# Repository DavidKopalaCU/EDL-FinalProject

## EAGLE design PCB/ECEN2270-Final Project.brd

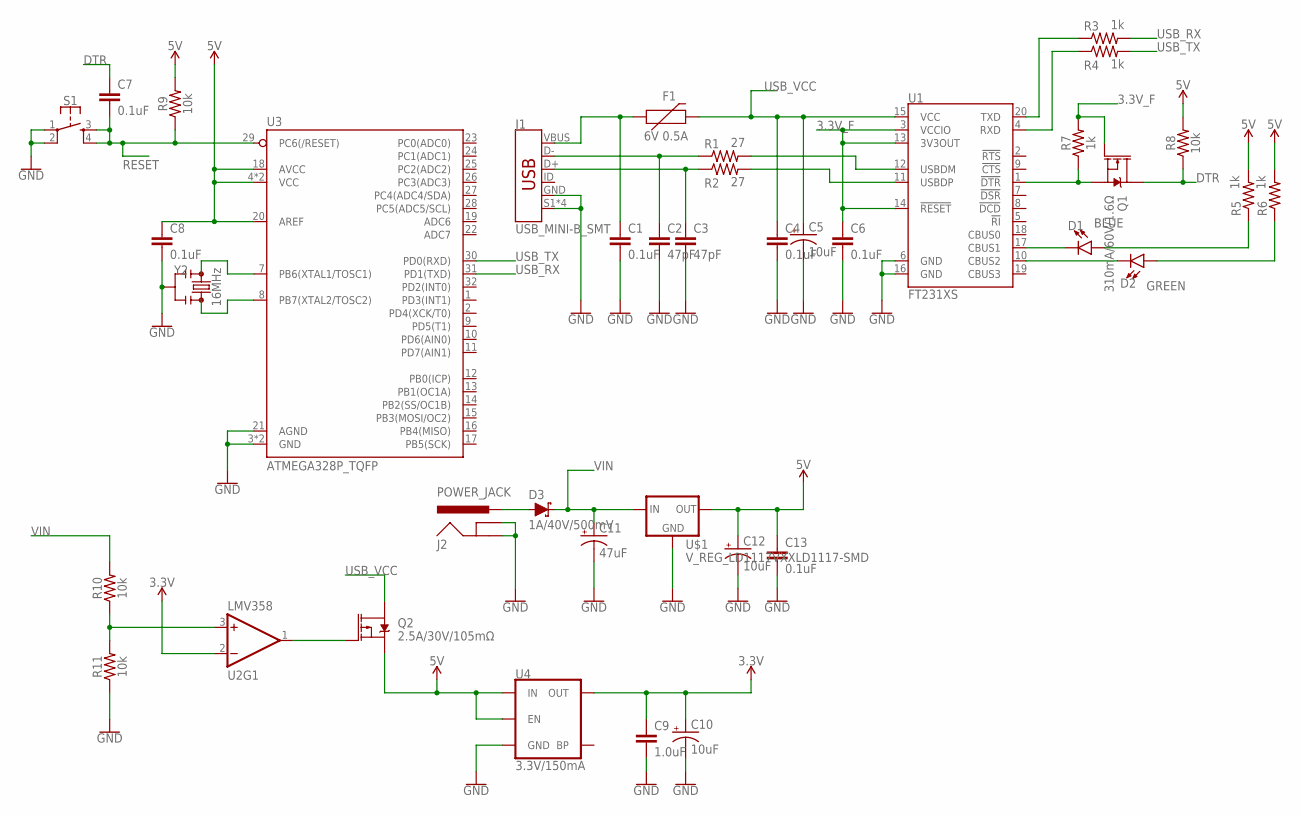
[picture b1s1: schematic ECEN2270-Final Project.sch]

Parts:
C1, C4, C6, C7, C8, C13: 0.1uF; 0603
C2, C3: 47pF; 0603
C5, C10, C12: 10uF; 0603-POLAR
C9: 1.0uF; 0603
C11: 47uF; CPOL-RADIAL-2.5MM-5MM
D1: BLUE; LED-0603
D2: GREEN; LED-0603
D3: 1A/40V/500mV; SMA-DIODE
F1: 6V 0.5A; 0805
J1: USB_MINI-B_SMT; USB-MINIB
J2: POWER_JACK; POWER_JACK_PTH
Q1: 310mA/60V/1.6Ω; SOT323
Q2: 2.5A/30V/105mΩ; SOT23-3
R1, R2: 27; 0603
R3, R4, R5, R6, R7: 1k; 0603
R8, R9, R10, R11: 10k; 0603
S1: MOMENTARY-SWITCH-SPST-2-SMD-5.2MM-TALL; TACTILE_SWITCH_SMD_5.2MM
U1: FT231XS; SSOP20_L
U2: LMV358; SO08
U3: ATMEGA328P_TQFP; TQFP32-08
U4: 3.3V/150mA; SOT23-5
U$1: V_REG_LD1117VXXLD1117-SMD; SOT223
Y2: 16MHz; RESONATOR-SMD-3.2X1.3

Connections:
3.3V: C9.1, C10.+, U2.2 (-IN), U4.5 (OUT)
3.3V_F: C6.1, Q1.1 (G), R7.2, U1.3 (VCCIO), U1.13 (3V3OUT), U1.14 (!RESET)
5V: C8.1, C12.+, C13.1, Q2.2 (S), R5.2, R6.2, R8.2, R9.2, U3.4 (VCC), U3.6 (VCC), U3.18 (AVCC), U3.20 (AREF), U4.1 (IN), U4.3 (EN), U$1.2 (OUT); also elsewhere on the board
DTR: C7.1, Q1.3 (D), R8.1
GND: C1.2, C2.2, C3.2, C4.2, C5.-, C6.2, C8.2, C9.2, C10.-, C11.2 (-), C12.-, C13.2, J1.GND, J1.S1 (SHIELD), J1.SHIELD1, J1.SHIELD2, J1.SHIELD3, J2.GND, J2.GNDBREAK, R11.1, S1.1, S1.2, U1.6 (GND), U1.16 (GND), U3.3 (GND), U3.5 (GND), U3.21 (AGND), U4.2 (GND), U$1.1 (GND), Y2.2; also elsewhere on the board
MISO: U3.16 (PB4(MISO)); also elsewhere on the board
MOSI: U3.15 (PB3(MOSI/OC2)); also elsewhere on the board
unnamed: C1.1, F1.1, J1.VBUS
unnamed: C2.1, J1.D-, R1.1
unnamed: R1.2, U1.12 (USBDM)
unnamed: C3.1, J1.D+, R2.1
unnamed: R2.2, U1.11 (USBDP)
unnamed: R3.1, U1.20 (TXD)
unnamed: R4.1, U1.4 (RXD)
unnamed: D1.C, U1.17 (CBUS1)
unnamed: D2.C, U1.10 (CBUS2)
unnamed: D1.A, R5.1
unnamed: D2.A, R6.1
unnamed: Q1.2 (S), R7.1, U1.1 (!DTR)
unnamed: U3.7 (PB6(XTAL1/TOSC1)), Y2.1
unnamed: U3.8 (PB7(XTAL2/TOSC2)), Y2.3
unnamed: R10.1, R11.2, U2.3 (+IN)
unnamed: Q2.1 (G), U2.1 (OUT)
unnamed: D3.A, J2.PWR
RESET: C7.2, R9.1, S1.3, S1.4, U3.29 (PC6(/RESET)); also elsewhere on the board
SCK: U3.17 (PB5(SCK)); also elsewhere on the board
USB_RX: R3.2, U3.31 (PD1(TXD))
USB_TX: R4.2, U3.30 (PD0(RXD))
USB_VCC: C4.1, C5.+, F1.2, Q2.3 (D), U1.15 (VCC)
VIN: C11.1 (+), D3.C, R10.2, U$1.3 (IN)

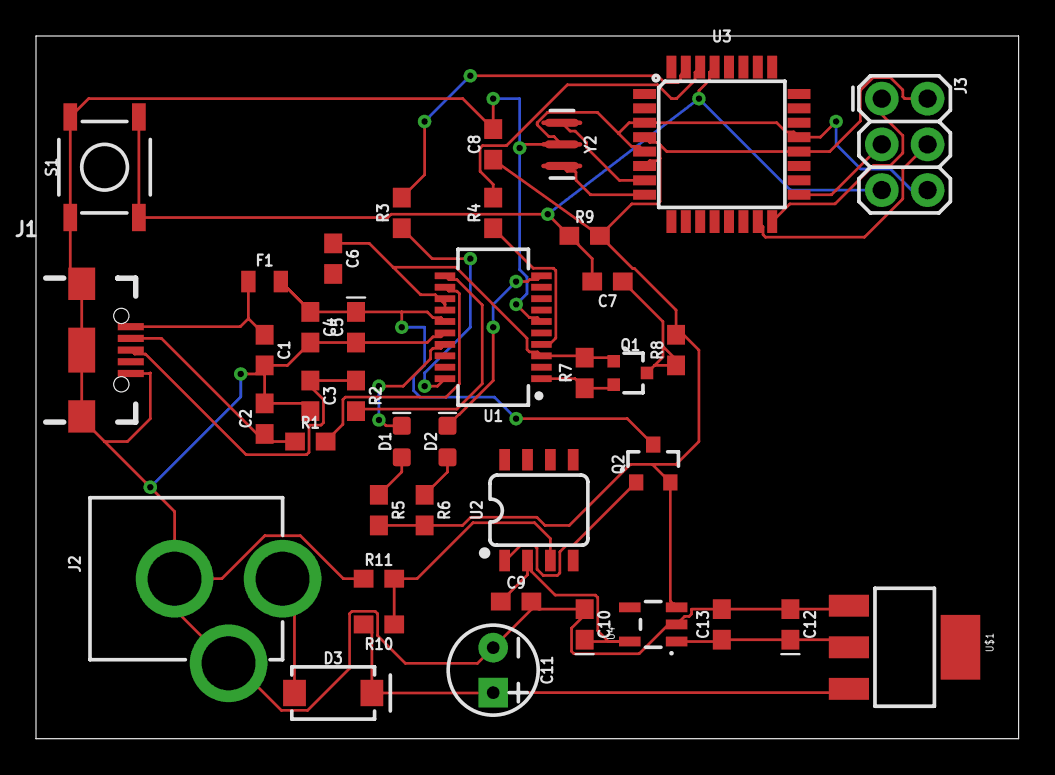
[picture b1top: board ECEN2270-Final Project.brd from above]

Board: 2 copper layers, 54.6 x 39.0 mm, 41 parts (0 on the bottom side), 30 nets.

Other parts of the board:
FRAME1: FRAME-LETTERNO_PACKAGE; DUMMY
J3: 2X3

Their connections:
5V: J3.2; also elsewhere on the board
GND: J3.6; also elsewhere on the board
MISO: J3.1; also elsewhere on the board
MOSI: J3.4; also elsewhere on the board
RESET: J3.5; also elsewhere on the board
SCK: J3.3; also elsewhere on the board

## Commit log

2019-04-09 Lab4 Demo Prep
2019-04-10 Finished Arduino clone
2019-04-10 Added ICSP Header For Arduino
2019-04-10 Replaced Mini USB with Micro

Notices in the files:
parts and their libraries:
SparkFun-Capacitors: Licensing: Creative Commons ShareAlike 4.0 International - https://creativecommons.org/licenses/by-sa/4.0
